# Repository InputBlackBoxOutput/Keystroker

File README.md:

# Keystroker
A USB HID device to perform USB drop attack

Research presented at BlackHat USA 2016 by Elie Bursztein of Google’s anti-abuse research team shows that the danger is alarmingly real!

[Watch this video to know more](https://www.youtube.com/watch?v=ZI5fvU5QKwQ&feature=emb_logo)

## How it works?

[Know more by reading these instructables](https://www.instructables.com/Keystroker-USB-Drop-Attack/)

## Steps to build the Keystroker 
1. Procure electronics components from a reliable source
1. Send the Gerber files to a PCB manufacturer to get a PCB made
1. 3D print the enclosure
1. Solder the components on the PCB, upload the firmware and test
1. Finally, mount the PCB in the enclosure

### Keystroker 3D render

### Demo 

## If you prefer using an Arduino Pro Micro
1. Remove the USB receptacle  
1. Use superglue to attach a USB type A plug
1. Connect the pins of the USB type A plug to the USB receptacle pads
1. Upload the firmware 

##  Useful modification ideas
- A hardware utility to securely store passwords and enter them when required
- A fully customized keyboard for a very specific purpose. For instance, a keyboard with video editor shortcuts as keys

### Made with lots of ⏱️, 📚 and ☕ by InputBlackBoxOutput

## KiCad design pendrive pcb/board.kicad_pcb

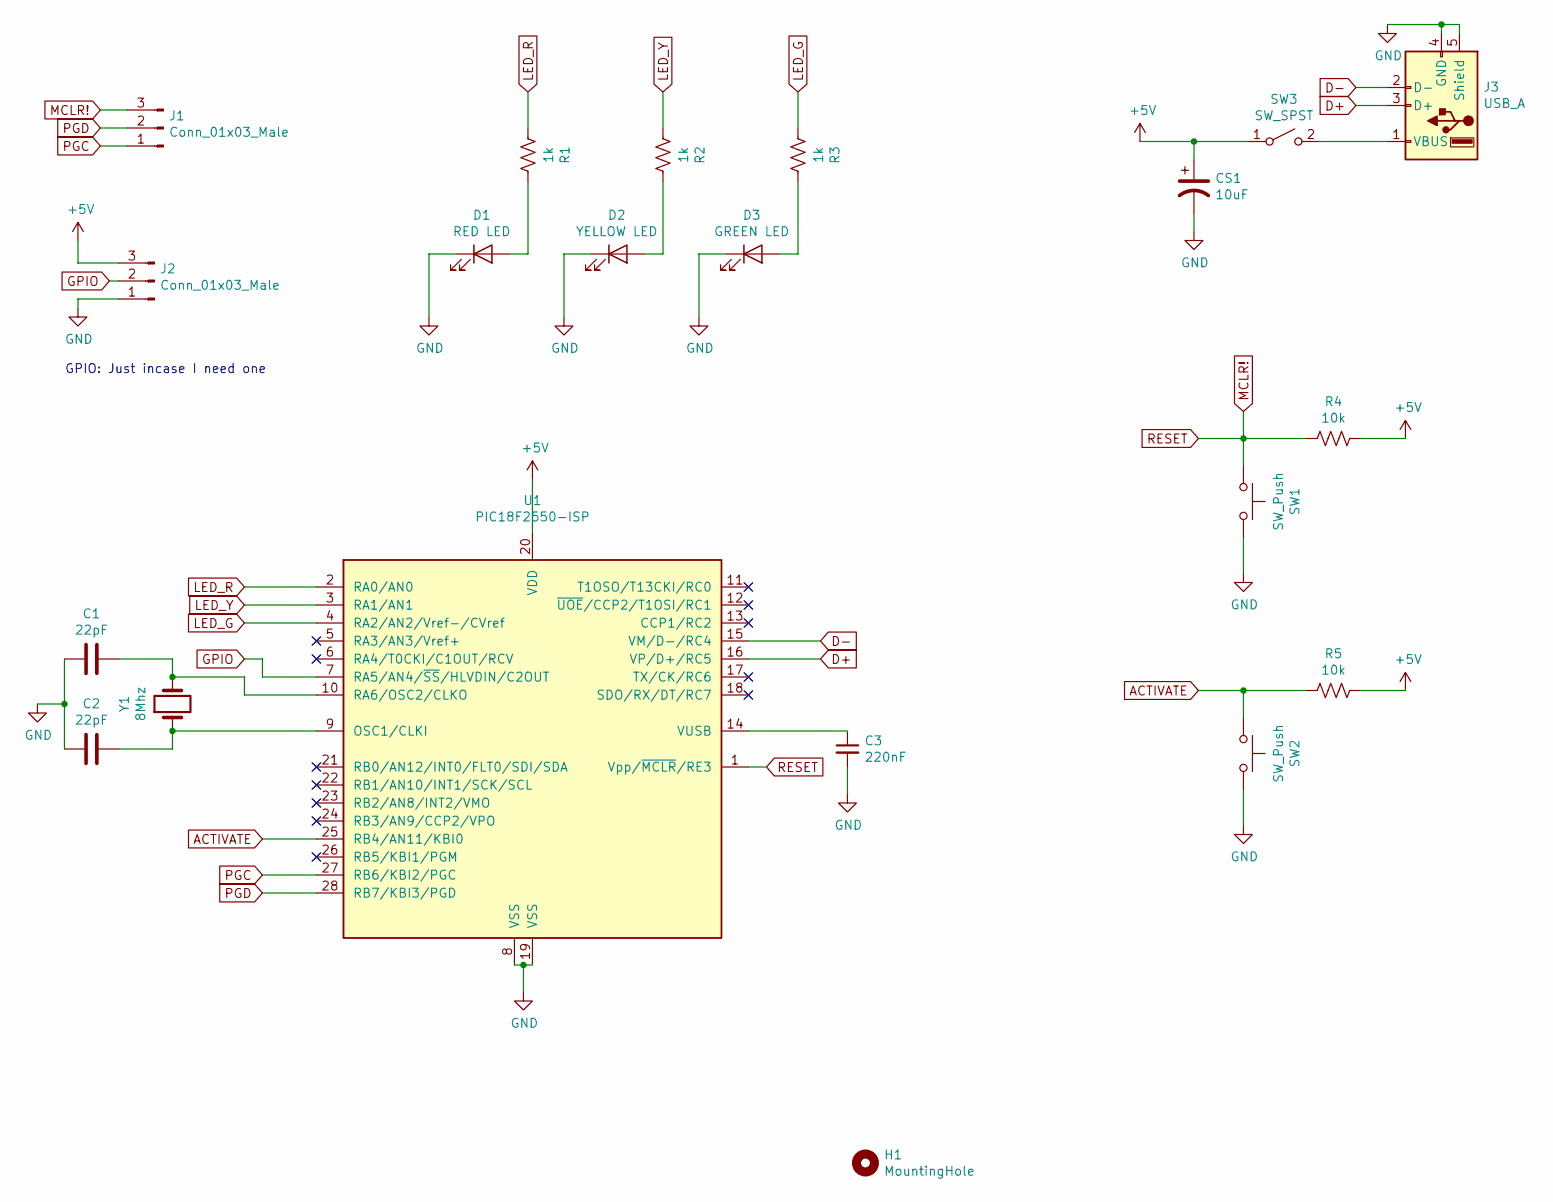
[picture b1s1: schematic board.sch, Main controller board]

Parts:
C1, C2: 22pF; C_0805_2012Metric_Pad1.15x1.40mm_HandSolder
C3: 220nF; C_0805_2012Metric_Pad1.15x1.40mm_HandSolder
CS1: 10uF; C_0805_2012Metric_Pad1.15x1.40mm_HandSolder
D1: RED LED; LED_0805_2012Metric_Pad1.15x1.40mm_HandSolder
D2: YELLOW LED; LED_0805_2012Metric_Pad1.15x1.40mm_HandSolder
D3: GREEN LED; LED_0805_2012Metric_Pad1.15x1.40mm_HandSolder
H1: MountingHole; MountingHole_2.1mm
J1, J2: Conn_01x03_Male; 3_pads
J3: USB_A; usb_pcb
R1, R2, R3: 1k; R_0805_2012Metric_Pad1.15x1.40mm_HandSolder
R4, R5: 10k; R_0805_2012Metric_Pad1.15x1.40mm_HandSolder
SW1, SW2: SW_Push; SW_SPST_B3U-1000P
SW3: SW_SPST; SW_SPST_EVQPE1
U1: PIC18F2550-ISP; SOIC-28W_7.5x17.9mm_P1.27mm
Y1: 8Mhz; Crystal_HC49-U_Vertical

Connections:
+5V: CS1.1, J2.3, R4.2, R5.2, SW3.1 (A), U1.20 (VDD)
ACTIVATE: R5.1, SW2.1, U1.25 (RB4/AN11/KBI0)
D+: J3.3 (D+), U1.16 (VP/D+/RC5)
D-: J3.2 (D-), U1.15 (VM/D-/RC4)
GND: C1.2, C2.2, C3.2, CS1.2, D1.1 (K), D2.1 (K), D3.1 (K), J2.1, J3.4 (GND), J3.5 (Shield), SW1.2, SW2.2, U1.8 (VSS), U1.19 (VSS)
GPIO: J2.2, U1.7 (RA5/AN4/~SS~/HLVDIN/C2OUT)
LED_G: R3.1, U1.4 (RA2/AN2/Vref-/CVref)
LED_R: R1.1, U1.2 (RA0/AN0)
LED_Y: R2.1, U1.3 (RA1/AN1)
MCLR!: J1.3, R4.1, SW1.1, U1.1 (Vpp/~MCLR~/RE3)
unnamed: C1.1, U1.10 (RA6/OSC2/CLKO), Y1.2
unnamed: C2.1, U1.9 (OSC1/CLKI), Y1.1
unnamed: C3.1, U1.14 (VUSB)
unnamed: D1.2 (A), R1.2
unnamed: D2.2 (A), R2.2
unnamed: D3.2 (A), R3.2
unnamed: J3.1 (VBUS), SW3.2 (B)
PGC: J1.1, U1.27 (RB6/KBI2/PGC)
PGD: J1.2, U1.28 (RB7/KBI3/PGD)

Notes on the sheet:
GPIO: Just incase I need one

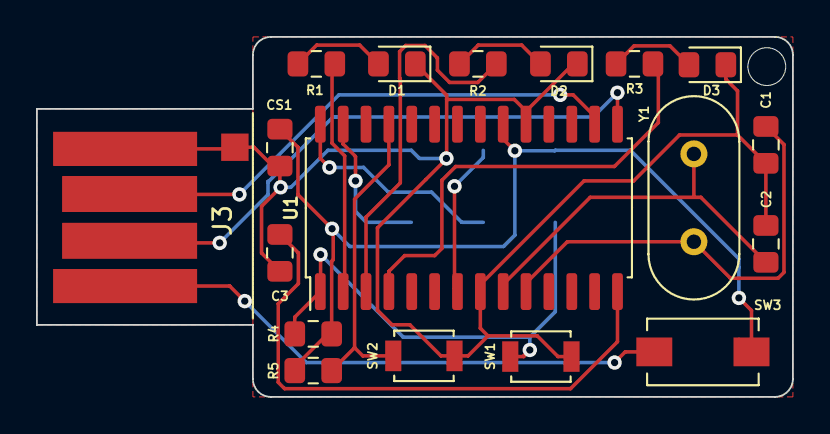
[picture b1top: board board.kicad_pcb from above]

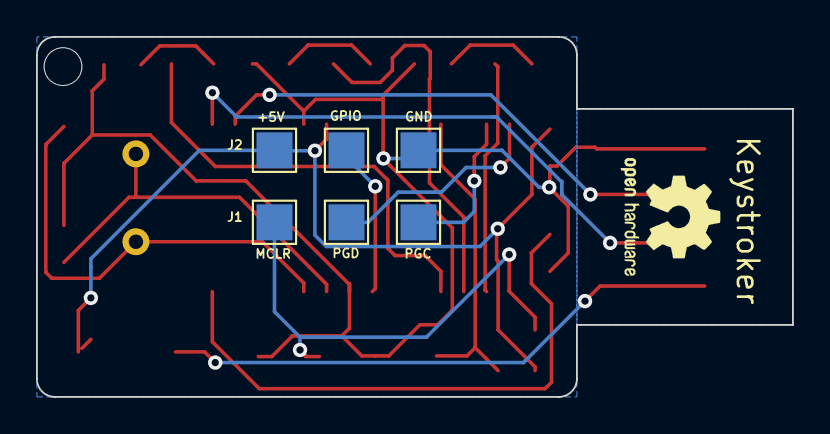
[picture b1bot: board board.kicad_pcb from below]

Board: 2 copper layers, 42.0 x 20.0 mm, 21 parts (2 on the bottom side), 19 nets.

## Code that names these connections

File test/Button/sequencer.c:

// LED sequencer

#define LED_R 0
#define LED_Y 1
#define LED_G 2
#define ON_DELAY  500 //ms

#define BTN RA4

void main() {
  int oldState;
  TRISB |= 1 << BTN;
  TRISA = 0x07;
  
  LATA = 0x00;

  while(1) {
      if(RA4 == 0) {
        if(oldState == 1)
            oldState = 0;
        else
            oldState = 1;
      }
      if(oldState == 1) {
         // Turn off all LEDS
         LATA &=~ (1 << LED_R || 1 << LED_Y || 1 << LED_G );
         
         // Turn on one by one
         LATA |= 1 << LED_G;
         Delay_ms(ON_DELAY);

         LATA |= 1 << LED_Y;
         Delay_ms(ON_DELAY);
         
         LATA |= 1 << LED_R;
         Delay_ms(ON_DELAY);
      }
      else {
         // Turn off all LEDS
         LATA &=~ (1 << LED_R || 1 << LED_Y || 1 << LED_G );
         
         // Turn on one by one
         LATA |= 1 << LED_R;
         Delay_ms(ON_DELAY);
         
         LATA |= 1 << LED_Y;
         Delay_ms(ON_DELAY);
         
         LATA |= 1 << LED_G;
         Delay_ms(ON_DELAY);
      }
  }
}

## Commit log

2021-01-06 PCB added
2021-01-06 Datasheets added
2021-01-06 Test codes added
2021-01-08 BOM and PCB 3D render added
2021-01-09 Ground plane added to PCB
2021-01-09 Payload added
2021-01-12 Info added to README
2021-01-14 Pendrive PCB added
2021-01-16 Switch moved to top
2021-01-16 3D model for enclosure added
2021-01-17 More images added
2021-01-21 INGAME firmware added
2021-01-22 README: Fixed 404
2021-02-05 Guy fawkes ASCII mask changed
2021-02-07 Guy Fawkes mask firmware added
2021-02-09 Arduino pro micro code added
2021-02-09 Images added
2021-02-13 README: Info added
2021-03-15 Typo fixed
2021-04-11 Demo GIF added
2021-04-11 Demo added to README
2021-06-17 README: Useful modification ideas added

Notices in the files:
PCB/board.sch:
Copyright 2019
